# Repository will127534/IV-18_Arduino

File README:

This program is to control MAX6921 for IV-18 VFD display 
To control the MAX6921 needs three pin,CLK,LOAD DATA,just like the shift regester
But the difference is MAX6921 is just using 19bit with LSB first.

Another thing is how you connect MAX6921 to the IV-18 tube.
the connection begin from the third one,with a,b,c,e,d,f,g,h,i
then comes with 1~9 digit.
the digit is already inverted(since LSB first)

The program also pack the DS1307 control (http://bildr.org/2011/03/ds1307-arduino/) to provide RTC .  

To enter the current time,just using the COM port and enter S, and you can enter the current time.

Here is the BLOG:(chinese)
http://will-123456.blogspot.tw/2014/01/iv-18-arduino-shield.html

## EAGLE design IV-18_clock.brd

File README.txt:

This program is to control MAX6921 for IV-18 VFD display 
To control the MAX6921 needs three pin,CLK,LOAD DATA,just like the shift regester
But the difference is MAX6921 is just using 19bit with LSB first.

Another thing is how you connect MAX6921 to the IV-18 tube.
the connection begin from the third one,with a,b,c,e,d,f,g,h,i
then comes with 1~9 digit.
the digit is already inverted(since LSB first)

The program also pack the DS1307 control (http://bildr.org/2011/03/ds1307-arduino/) to provide RTC servce.  

Here is the BLOG:(chinese)
http://will-123456.blogspot.tw/2014/01/iv-18-arduino-shield.html

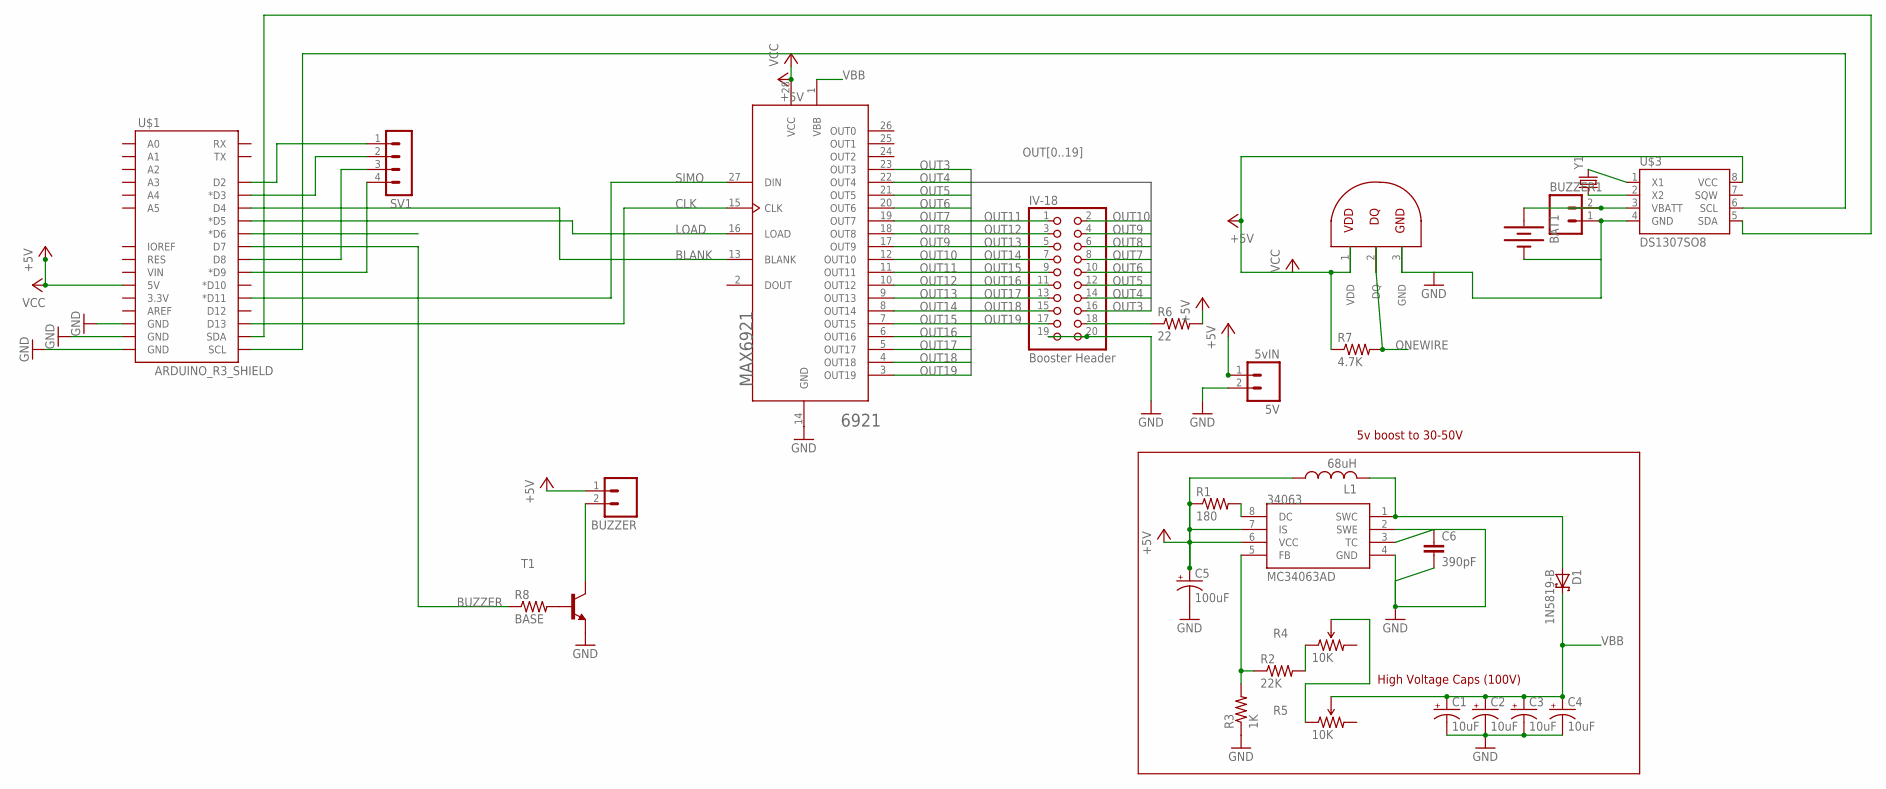
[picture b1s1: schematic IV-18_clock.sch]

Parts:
5V: 5vIN; 1X02
6921: MAX6921_AFSOIC(W); SO28L
34063: MC34063AD; SOIC8
BAT1: BATTERY20PTH; BATTCOM_20MM_PTH
BUZZER, BUZZER1: 1X02
C1, C2, C3, C4: 10uF; E2,5-6
C5: 100uF; E2,5-6
C6: 390pF; CAP-PTH-5MM
D1: 1N5819-B; DO41-7.6
DS18B20: DS18B20; TO92-CBE@1
IV-18: Booster Header; 2X10
L1: 68uH; 6000-XXXX-RC
R1: 180; 0204/7
R2: 22K; 0204/7
R3: 1K; 0204/7
R4, R5: 10K; TRIM_POT_PTH
R6: 22; 0204/7
R7: 4.7K; 0204/7
R8: BASE; 0204/7
SV1: MA04-1
T1: TO92-EBC
U$1: ARDUINO_R3_SHIELD; UNO_R3_SHIELD
U$3: DS1307SO8; SO08
Y1: CRYSTALTC26H_EZ; TC26HEZ

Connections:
+5V: 5V.1, 6921.28 (VCC), 34063.6 (VCC), 34063.7 (IS), BUZZER.1, C5.+, DS18B20.1 (VDD), L1.1, R1.1, R6.2, R7.1, U$1.5V, U$3.8 (VCC)
BLANK: 6921.13 (BLANK), U$1.D4
BUZZER: R8.1, U$1.D7
CLK: 6921.15 (CLK), U$1.D13
GND: 5V.2, 6921.14 (GND), 34063.2 (SWE), 34063.4 (GND), BAT1.2 (-), BUZZER1.1, C1.-, C2.-, C3.-, C4.-, C5.-, C6.2, DS18B20.3 (GND), IV-18.19, IV-18.20, R3.1, T1.E, U$1.GND@0 (GND), U$1.GND@1 (GND), U$1.GND@2 (GND), U$3.4 (GND)
LOAD: 6921.16 (LOAD), U$1.D5 (*D5)
unnamed: IV-18.18, R6.1
unnamed: R2.2, R4.1 (CCW)
unnamed: 34063.1 (SWC), D1.A, L1.2
unnamed: R4.2 (WIPER), R5.1 (CCW)
unnamed: 34063.8 (DC), R1.2
unnamed: 34063.3 (TC), C6.1
unnamed: 34063.5 (FB), R2.1, R3.2
unnamed: R8.2, T1.B
unnamed: SV1.1, U$1.D2
unnamed: SV1.2, U$1.D3 (*D3)
unnamed: SV1.3, U$1.D8
unnamed: BUZZER.2, T1.C
unnamed: U$3.1 (X1), Y1.2
unnamed: U$3.2 (X2), Y1.1
unnamed: U$1.SCL, U$3.6 (SCL)
unnamed: BAT1.1 (+), BUZZER1.2, U$3.3 (VBATT)
unnamed: U$1.SDA, U$3.5 (SDA)
unnamed: SV1.4, U$1.D9 (*D9)
ONEWIRE: DS18B20.2 (DQ), R7.2, U$1.D6 (*D6)
OUT3: 6921.23 (OUT3), IV-18.16
OUT4: 6921.22 (OUT4), IV-18.14
OUT5: 6921.21 (OUT5), IV-18.12
OUT6: 6921.20 (OUT6), IV-18.10
OUT7: 6921.19 (OUT7), IV-18.8
OUT8: 6921.18 (OUT8), IV-18.6
OUT9: 6921.17 (OUT9), IV-18.4
OUT10: 6921.12 (OUT10), IV-18.2
OUT11: 6921.11 (OUT11), IV-18.1
OUT12: 6921.10 (OUT12), IV-18.3
OUT13: 6921.9 (OUT13), IV-18.5
OUT14: 6921.8 (OUT14), IV-18.7
OUT15: 6921.7 (OUT15), IV-18.9
OUT16: 6921.6 (OUT16), IV-18.11
OUT17: 6921.5 (OUT17), IV-18.13
OUT18: 6921.4 (OUT18), IV-18.15
OUT19: 6921.3 (OUT19), IV-18.17
SIMO: 6921.27 (DIN), U$1.D11 (*D11)
VBB: 6921.1 (VBB), C1.+, C2.+, C3.+, C4.+, D1.C, R5.2 (WIPER)

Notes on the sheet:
5v boost to 30-50V
High Voltage Caps (100V)

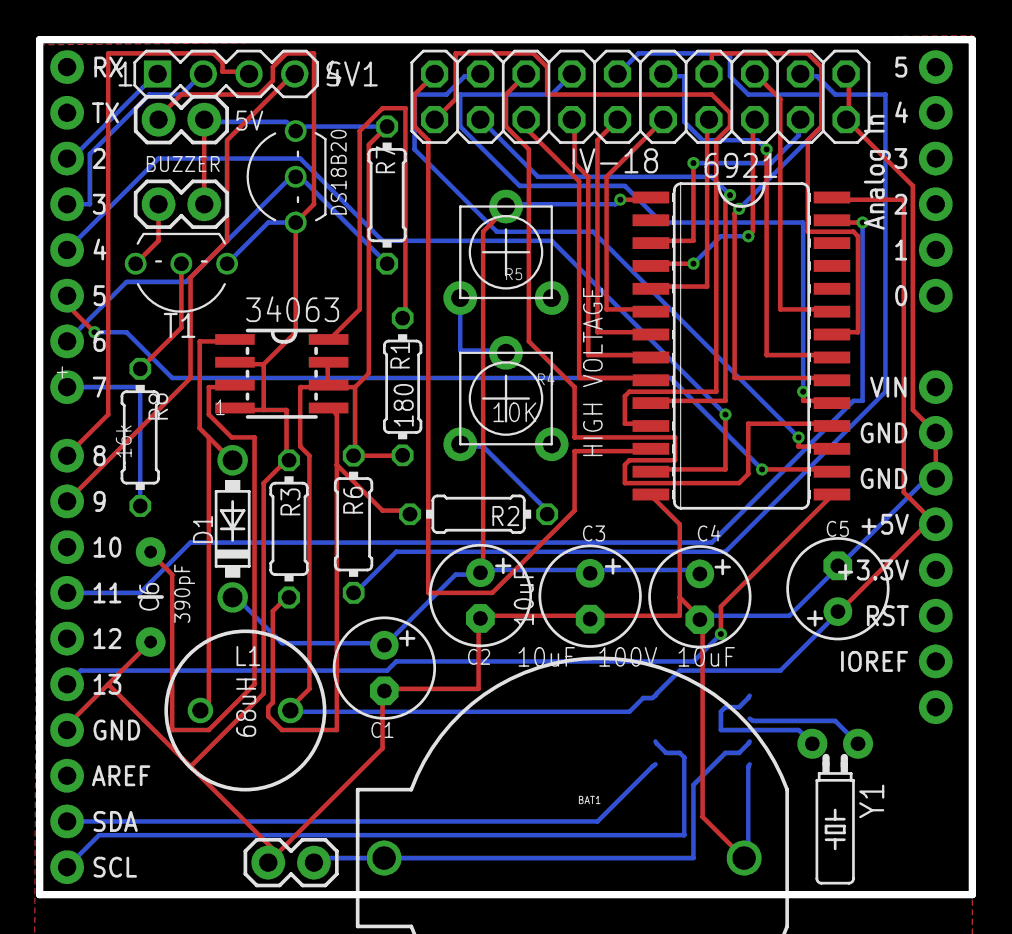
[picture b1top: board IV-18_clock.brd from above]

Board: 2 copper layers, 51.8 x 47.5 mm, 29 parts (1 on the bottom side), 44 nets.

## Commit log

2014-02-01 Ver 1.0
    First working program on the IV-18 Arduino Shield
2014-02-01 Ver 1.0
2014-08-10 Ver 1.1
    adding a switch to turn off the display
    also adding PCB file
2014-08-10 Ver 1.1

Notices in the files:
parts and their libraries:
SparkFun: Licensing: CC v3.0 Share-Alike You are welcome to use this library for commercial purposes.
